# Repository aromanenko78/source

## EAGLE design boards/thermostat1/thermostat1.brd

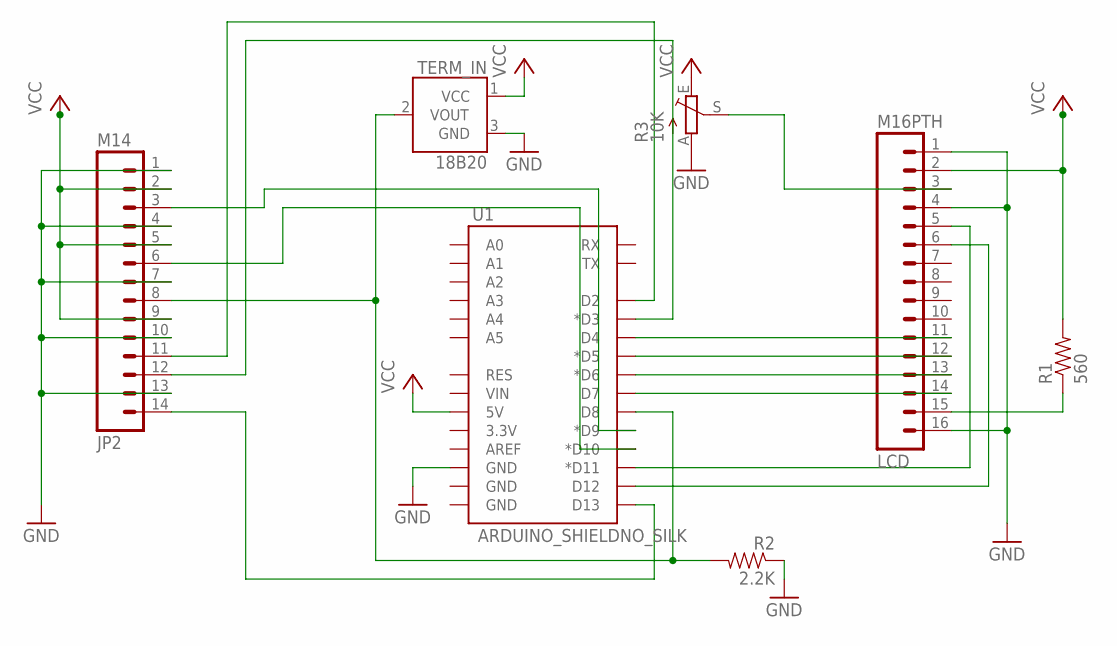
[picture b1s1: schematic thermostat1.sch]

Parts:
JP2: M14; 1X14
LCD: M16PTH; 1X16
R1: 560; AXIAL-0.5
R2: 2.2K; AXIAL-0.5
R3: 10K; CA6V
TERM_IN: 18B20; TO-92
U1: ARDUINO_SHIELDNO_SILK; DUEMILANOVE_VIAS

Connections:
GND: JP2.1, JP2.4, JP2.7, JP2.10, JP2.13, LCD.1, LCD.4, LCD.16, R2.P$1 (1), R3.A, TERM_IN.3 (GND), U1.GND@2 (GND)
unnamed: LCD.3, R3.S
unnamed: LCD.14, U1.D7
unnamed: LCD.13, U1.D6 (*D6)
unnamed: LCD.15, R1.P$1 (1)
unnamed: LCD.6, U1.D12
unnamed: LCD.5, U1.D11 (*D11)
unnamed: LCD.12, U1.D5 (*D5)
unnamed: LCD.11, U1.D4
unnamed: JP2.3, U1.D9 (*D9)
unnamed: JP2.6, U1.D10 (*D10)
unnamed: JP2.11, U1.D2
unnamed: JP2.12, U1.D3 (*D3)
unnamed: JP2.14, U1.D13
unnamed: JP2.8, R2.P$2 (2), TERM_IN.2 (VOUT), U1.D8
VCC: JP2.2, JP2.5, JP2.9, LCD.2, R1.P$2 (2), R3.E, TERM_IN.1 (VCC), U1.5V

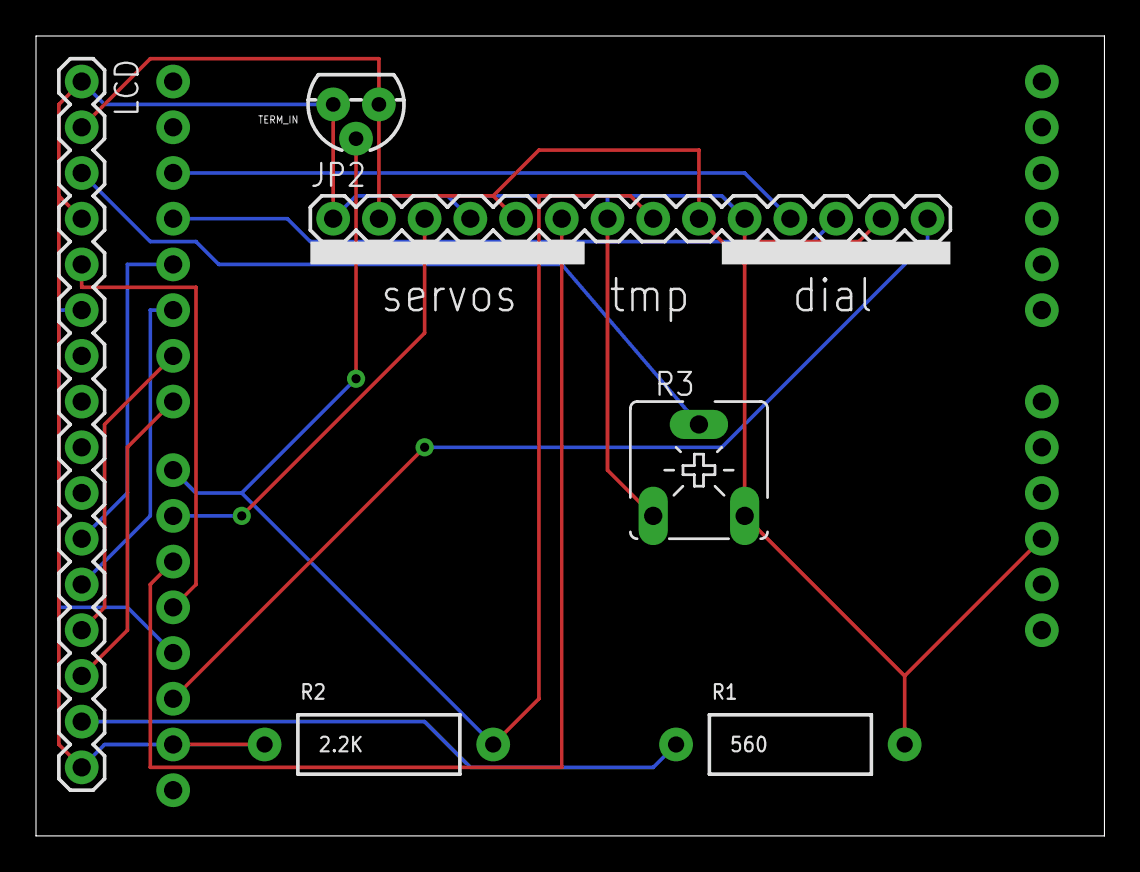
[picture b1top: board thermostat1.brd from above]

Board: 2 copper layers, 59.4 x 44.4 mm, 7 parts (0 on the bottom side), 16 nets.

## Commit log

2014-09-21 Initial repo
2014-09-21 adding print boards
2014-09-21 Added heater library (skeleton)
2014-09-23 Factored out Heater
    compiles, not tested
2014-09-24 Fixed heat/flow clicks issue
2014-09-24 Encoder library. Builds, handlers not wired up.
2014-09-25 Fix target temp bug
2014-09-25 Encoder fixes (not connected, not tested)
2014-09-25 Encoder connected and tested
2014-10-02 Declared target as a constant
2014-11-18 Fixing cold weather warmup
2014-11-30 Added MAX and MIN settings

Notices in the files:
parts and their libraries:
SparkFun-Boards: Licensing: CC v3.0 Share-Alike You are welcome to use this library for commercial purposes.
